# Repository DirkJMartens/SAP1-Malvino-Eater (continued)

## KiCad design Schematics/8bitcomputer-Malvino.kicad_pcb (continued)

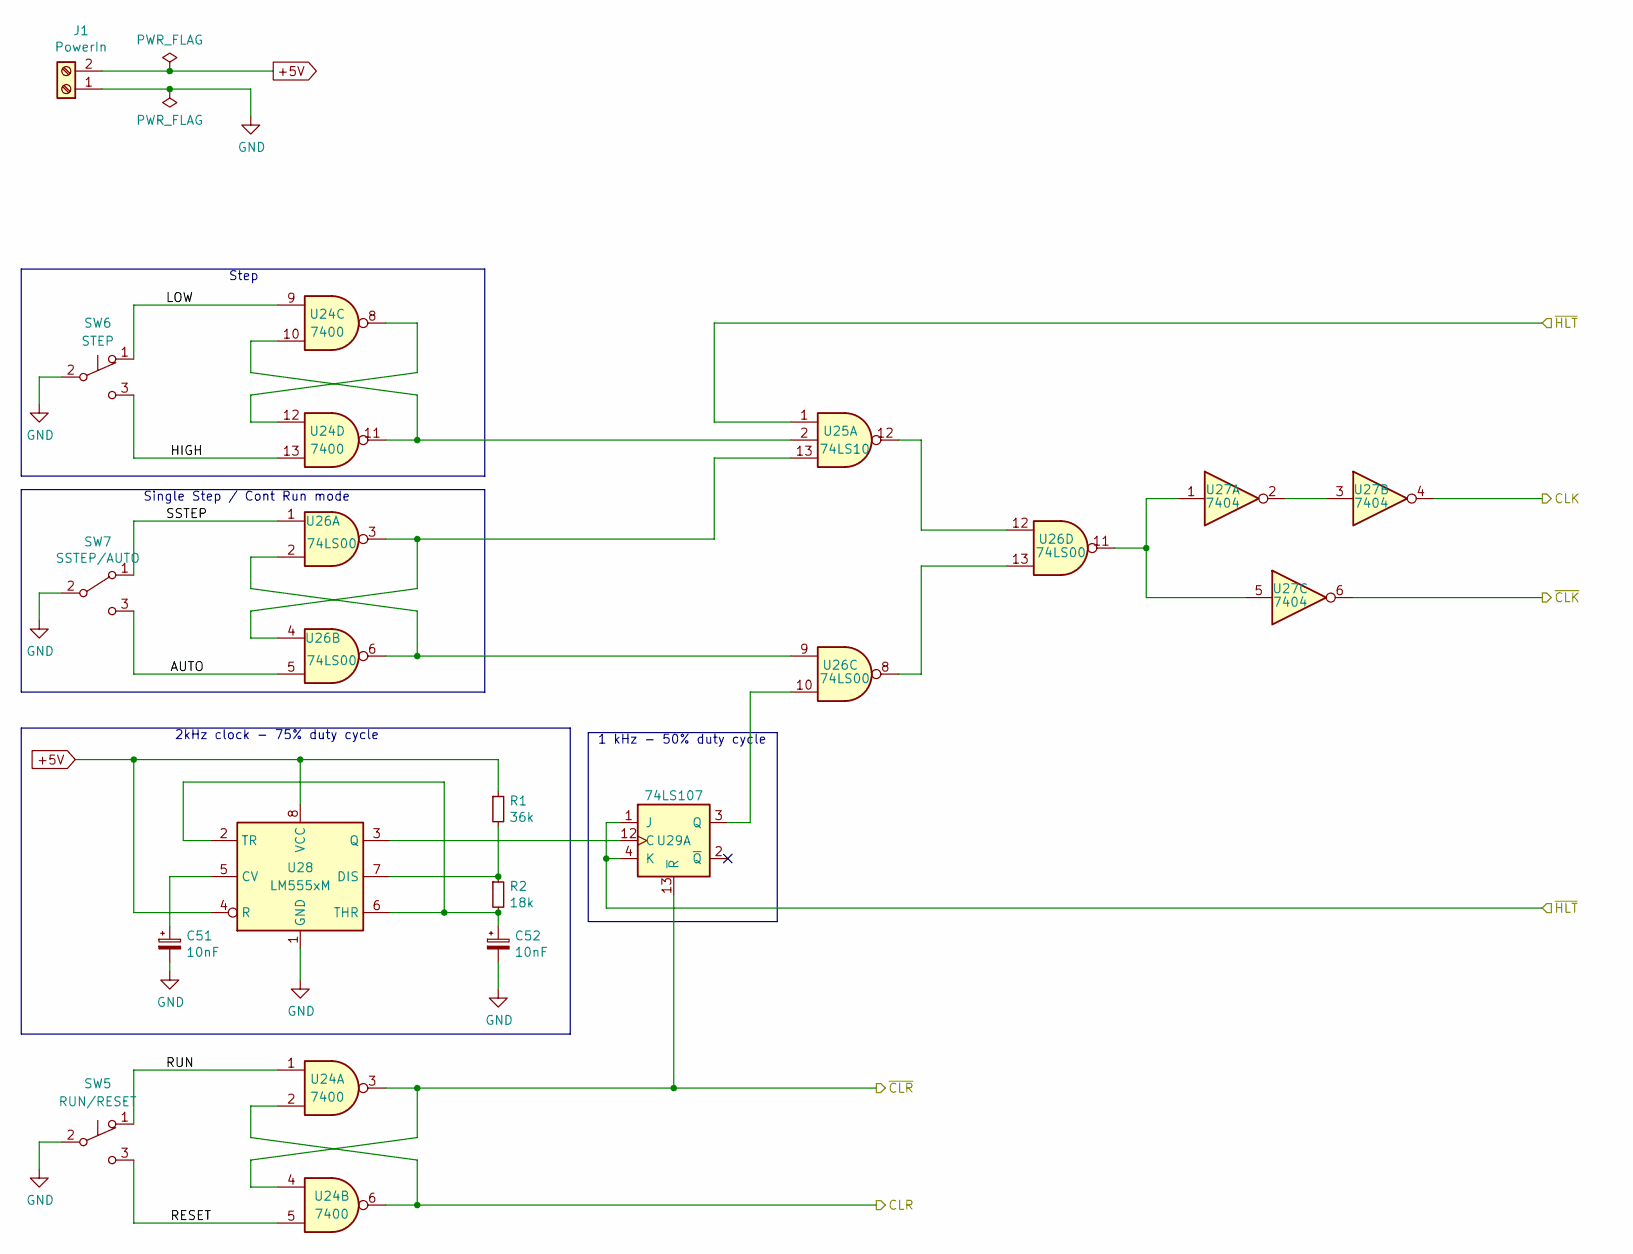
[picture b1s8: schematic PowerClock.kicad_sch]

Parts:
C51, C52: 10nF; C_Disc_D7.5mm_W5.0mm_P7.50mm
J1: PowerIn; TerminalBlock_Phoenix_MKDS-1,5-2-5.08_1x02_P5.08mm_Horizont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
R1: 36k; R_Axial_DIN0207_L6.3mm_D2.5mm_P7.62mm_Horizontal
R2: 18k; R_Axial_DIN0207_L6.3mm_D2.5mm_P7.62mm_Horizontal
SW5: RUN/RESET; SW_Push_1P2T_Vertical_E-Switch_800UDP8P1A1M6
SW6: STEP; SW_CuK_OS102011MA1QN1_SPDT_Angled
SW7: SSTEP/AUTO; TerminalBlock_Phoenix_MKDS-1,5-3-5.08_1x03_P5.08mm_Horizont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
U24: 7400; DIP-14_W7.62mm_LongPads
U25: 74LS10; DIP-14_W7.62mm_LongPads
U26: 74LS00; DIP-14_W7.62mm_LongPads
U27: 7404; DIP-14_W7.62mm_LongPads
U28: LM555xM; DIP-8_W7.62mm_LongPads
U29: 74LS107; DIP-14_W7.62mm_LongPads

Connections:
+5V: J1.2, R1.1, U28.4 (R), U28.8 (VCC); also elsewhere on the board
/1-PowerClock/AUTO: SW7.3 (C), U26.5
/1-PowerClock/CLK: U27.4; also elsewhere on the board
/1-PowerClock/CLR: U24.2, U24.6; also elsewhere on the board
/1-PowerClock/HIGH: SW6.3 (C), U24.13
/1-PowerClock/LOW: SW6.1 (A), U24.9
/1-PowerClock/RESET: SW5.3 (C), U24.5
/1-PowerClock/RUN: SW5.1 (A), U24.1
/1-PowerClock/SSTEP: SW7.1 (A), U26.1
/1-PowerClock/~CLK: U27.6
/1-PowerClock/~CLR: U24.3, U24.4, U29.13 (~R); also elsewhere on the board
/1-PowerClock/~HLT: U25.1, U29.1 (J), U29.4 (K); also elsewhere on the board
GND: C51.2, C52.2, J1.1, SW5.2 (B), SW6.2 (B), SW7.2 (B), U28.1 (GND); also elsewhere on the board
unnamed: C51.1, U28.5 (CV)
unnamed: C52.1, R2.2, U28.2 (TR), U28.6 (THR)
unnamed: R1.2, R2.1, U28.7 (DIS)
unnamed: U24.10, U24.11, U25.2
unnamed: U24.8, U24.12
unnamed: U25.12, U26.12
unnamed: U25.13, U26.3, U26.4
unnamed: U26.2, U26.6, U26.9
unnamed: U26.10, U29.3 (Q)
unnamed: U26.11, U27.1, U27.5
unnamed: U26.8, U26.13
unnamed: U27.2, U27.3
unnamed: U28.3 (Q), U29.12 (C)

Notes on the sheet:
Step
2kHz clock - 75% duty cycle
1 kHz - 50% duty cycle
Single Step / Cont Run mode

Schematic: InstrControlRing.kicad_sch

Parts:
D1, D2, D3, D4, D5, D6: Grn; LED_D3.0mm
D7: Cp; LED_D3.0mm
D8: Ep; LED_D3.0mm
D9: Lm; LED_D3.0mm
D14: CE; LED_D3.0mm
D15: Li; LED_D3.0mm
D16: Ei; LED_D3.0mm
D17: La; LED_D3.0mm
D18: Ea; LED_D3.0mm
D19: Su; LED_D3.0mm
D20: Eu; LED_D3.0mm
D21: Lb; LED_D3.0mm
D22: L0; LED_D3.0mm
D23: HLT; LED_D3.0mm
D24: OUT; LED_D3.0mm
D25: SUB; LED_D3.0mm
D26: ADD; LED_D3.0mm
D27: LDA; LED_D3.0mm
R3, R4, R5, R6, R7, R8, R9, R10, R16, R17, R18, R19, R20, R21, R22, R23, R24, R25, R26, R27, R28, R29, R30: 620; R_0805_2012Metric
U31, U35, U47, U48, U49: 74LS04; DIP-14_W7.62mm_LongPads
U32, U33, U34, U44: 74LS20; DIP-14_W7.62mm_LongPads
U36, U37, U38: 74LS107; DIP-14_W7.62mm_LongPads
U39, U40, U41, U42, U43, U46: 74LS00; DIP-14_W7.62mm_LongPads
U45: 74LS10; DIP-14_W7.62mm_LongPads

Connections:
/1-PowerClock/CLK: U36.9 (C), U36.12 (C), U37.9 (C), U37.12 (C), U38.9 (C), U38.12 (C); also elsewhere on the board
/1-PowerClock/~CLR: U36.10 (~R), U36.13 (~R), U37.10 (~R), U37.13 (~R), U38.10 (~R), U38.13 (~R); also elsewhere on the board
/1-PowerClock/~HLT: D23.2 (A), U34.6; also elsewhere on the board
/2-ProgramCounter/~Ep: U47.2; also elsewhere on the board
/3-InputAndMAR/~Lm: D9.2 (A), U48.6; also elsewhere on the board
/4-16x8RAM/RUN: D14.2 (A), U47.4; also elsewhere on the board
/5-InstructionRegister/I4: U31.9, U32.13, U34.5; also elsewhere on the board
/5-InstructionRegister/I5: U31.5, U33.4, U33.12, U34.4; also elsewhere on the board
/5-InstructionRegister/I6: U31.3, U33.10, U34.2; also elsewhere on the board
/5-InstructionRegister/I7: U31.1, U33.9, U34.1; also elsewhere on the board
/5-InstructionRegister/~Ei: D16.2 (A), U47.8; also elsewhere on the board
/5-InstructionRegister/~Li: D15.2 (A), U47.6; also elsewhere on the board
/6-AccuAddSub/Su: D19.2 (A), U48.2; also elsewhere on the board
/6-AccuAddSub/~Ea: U49.2; also elsewhere on the board
/6-AccuAddSub/~Eu: U49.4; also elsewhere on the board
/6-AccuAddSub/~La: D17.2 (A), U47.10; also elsewhere on the board
/7-RegisterB/~Lb: D21.2 (A), U48.4; also elsewhere on the board
/8-OutputRegister/~Lo: D22.2 (A), U43.8, U48.9; also elsewhere on the board
/9-InstrControlRing/ADD: D26.2 (A), U35.4, U39.4, U40.1, U40.12, U41.9, U42.9, U43.1
/9-InstrControlRing/Ea: D18.2 (A), U47.12, U49.1
/9-InstrControlRing/Eu: D20.2 (A), U46.3, U49.3
/9-InstrControlRing/LDA: D27.2 (A), U35.2, U39.1, U39.12, U40.9, U41.4
/9-InstrControlRing/Lo: U48.8
/9-InstrControlRing/OUT: D24.2 (A), U35.8, U42.1, U43.9
/9-InstrControlRing/SUB: D25.2 (A), U35.6, U39.9, U40.4, U41.1, U41.12, U42.4, U42.12, U43.4
/9-InstrControlRing/T1: D1.2 (A), D8.2 (A), U35.11, U38.1 (J), U38.6 (~Q), U47.1
/9-InstrControlRing/T2: D2.2 (A), D7.2 (A), U37.8 (J), U38.3 (Q); also elsewhere on the board
/9-InstrControlRing/T3: D3.2 (A), U35.13, U37.1 (J), U37.5 (Q), U47.5
/9-InstrControlRing/T4: D4.2 (A), U36.8 (J), U37.3 (Q), U39.2, U39.5, U39.10, U40.10, U40.13, U41.2, U42.2, U43.10
/9-InstrControlRing/T5: D5.2 (A), U36.1 (J), U36.5 (Q), U39.13, U40.2, U40.5, U41.5, U43.2, U43.5
/9-InstrControlRing/T6: D6.2 (A), U36.3 (Q), U38.11 (K), U41.10, U41.13, U42.5, U42.10, U42.13
GND: R3.2, R4.2, R5.2, R6.2, R7.2, R8.2, R9.2, R10.2, R16.2, R17.2, R18.2, R19.2, R20.2, R21.2, R22.2, R23.2, R24.2, R25.2, R26.2, R27.2, R28.2, R29.2, R30.2; also elsewhere on the board
unnamed: D1.1 (K), R3.1
unnamed: D2.1 (K), R4.1
unnamed: D3.1 (K), R5.1
unnamed: D4.1 (K), R6.1
unnamed: D5.1 (K), R7.1
unnamed: D6.1 (K), R8.1
unnamed: D7.1 (K), R9.1
unnamed: D8.1 (K), R10.1
unnamed: D9.1 (K), R16.1
unnamed: D14.1 (K), R17.1
unnamed: D15.1 (K), R18.1
unnamed: D16.1 (K), R19.1
unnamed: D17.1 (K), R20.1
unnamed: D18.1 (K), R21.1
unnamed: D19.1 (K), R22.1
unnamed: D20.1 (K), R23.1
unnamed: D21.1 (K), R24.1
unnamed: D22.1 (K), R25.1
unnamed: D23.1 (K), R26.1
unnamed: D24.1 (K), R27.1
unnamed: D25.1 (K), R28.1
unnamed: D26.1 (K), R29.1
unnamed: D27.1 (K), R30.1
unnamed: U31.2, U32.1, U32.9, U33.1
unnamed: U31.4, U32.2, U32.10, U33.2
unnamed: U31.6, U32.4, U32.12
unnamed: U31.8, U32.5, U33.5, U33.13
unnamed: U32.6, U35.1
unnamed: U32.8, U35.3
unnamed: U33.6, U35.5
unnamed: U33.8, U35.9
unnamed: U35.10, U44.1
unnamed: U35.12, U44.9
unnamed: U36.2 (~Q), U38.8 (J)
unnamed: U36.4 (K), U36.6 (~Q)
unnamed: U36.11 (K), U37.2 (~Q)
unnamed: U37.4 (K), U37.6 (~Q)
unnamed: U37.11 (K), U38.2 (~Q)
unnamed: U38.4 (K), U38.5 (Q)
unnamed: U39.3, U44.2
unnamed: U39.6, U44.4
unnamed: U39.8, U44.5
unnamed: U39.11, U44.10
unnamed: U40.3, U44.12
unnamed: U40.6, U44.13
unnamed: U40.8, U45.13
unnamed: U40.11, U45.2
unnamed: U41.3, U45.1
unnamed: U41.6, U45.5
unnamed: U41.8, U45.4
unnamed: U41.11, U45.3
unnamed: U42.3, U47.13
unnamed: U42.6, U48.1
unnamed: U42.8, U46.1
unnamed: U42.11, U46.2
unnamed: U43.3, U46.4
unnamed: U43.6, U46.5
unnamed: U44.6, U48.5
unnamed: U44.8, U47.3
unnamed: U45.6, U47.11
unnamed: U45.12, U47.9
unnamed: U46.6, U48.3

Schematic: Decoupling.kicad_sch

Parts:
C1, C2, C3, C4, C5, C6, C7, C8, C9, C10, C11, C12, C13, C14, C15, C16, C17, C18, C19, C20, C21, C22, C23, C24, C25, C26, C27, C28, C29, C31, C32, C33, C34, C35, C36, C37, C38, C39, C40, C41, C42, C43, C44, C45, C46, C47, C48: 100nF; C_0805_2012Metric
U1, U2, U29: 74LS107; DIP-14_W7.62mm_LongPads
U24: 7400; DIP-14_W7.62mm_LongPads
U25, U45: 74LS10; DIP-14_W7.62mm_LongPads
U26: 74LS00; DIP-14_W7.62mm_LongPads
U27: 7404; DIP-14_W7.62mm_LongPads
U32, U33, U34, U44: 74LS20; DIP-14_W7.62mm_LongPads

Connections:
+5: C6.1, C7.1; also elsewhere on the board
+5V: C1.1, C2.1, C3.1, C4.1, C5.1, C8.1, C9.1, C10.1, C11.1, C12.1, C13.1, C14.1, C15.1, C16.1, C17.1, C18.1, C19.1, C20.1, C21.1, C22.1, C23.1, C24.1, C25.1, C26.1, C27.1, C28.1, C29.1, C31.1, C32.1, C33.1, C34.1, C35.1, C36.1, C37.1, C38.1, C39.1, C40.1, C41.1, C42.1, C43.1, C44.1, C45.1, C46.1, C47.1, C48.1, U1.14 (VCC), U2.14 (VCC), U24.14 (VCC), U25.14 (VCC), U26.14 (VCC), U27.14 (VCC), U29.14 (VCC), U32.14 (VCC), U33.14 (VCC), U34.14 (VCC), U44.14 (VCC), U45.14 (VCC); also elsewhere on the board
GND: C1.2, C2.2, C3.2, C4.2, C5.2, C6.2, C7.2, C8.2, C9.2, C10.2, C11.2, C12.2, C13.2, C14.2, C15.2, C16.2, C17.2, C18.2, C19.2, C20.2, C21.2, C22.2, C23.2, C24.2, C25.2, C26.2, C27.2, C28.2, C29.2, C31.2, C32.2, C33.2, C34.2, C35.2, C36.2, C37.2, C38.2, C39.2, C40.2, C41.2, C42.2, C43.2, C44.2, C45.2, C46.2, C47.2, C48.2, U1.7 (GND), U2.7 (GND), U24.7 (GND), U25.7 (GND), U26.7 (GND), U27.7 (GND), U29.7 (GND), U32.7 (GND), U33.7 (GND), U34.7 (GND), U44.7 (GND), U45.7 (GND); also elsewhere on the board

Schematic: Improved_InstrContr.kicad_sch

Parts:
U101, U102, U103, U104, U105: (no value)

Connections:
unnamed: U101.3, U105.3
unnamed: U101.4, U101.9, U103.3, U103.4
unnamed: U101.5, U102.4
unnamed: U101.6, U103.12, U105.13
unnamed: U101.7 (GND), U102.7 (GND), U103.7 (GND), U104.7 (GND), U105.7 (GND)
unnamed: U101.8, U104.8
unnamed: U101.10, U102.2
unnamed: U101.11, U104.2, U105.9
unnamed: U101.2, U101.12
unnamed: U101.13, U103.6
unnamed: U101.14 (VCC), U102.14 (VCC), U103.14 (VCC), U104.14 (VCC), U105.14 (VCC)
unnamed: U102.1, U103.2
unnamed: U102.5, U103.5
unnamed: U102.6, U103.13, U104.9
unnamed: U102.9, U102.10, U102.12, U102.13, U103.9, U103.10
unnamed: U103.11, U104.5
unnamed: U104.1, U104.11
unnamed: U104.4, U105.11
unnamed: U104.6, U105.1
unnamed: U104.10, U105.5

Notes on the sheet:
Ep = T1 Cp = T2 Li = T3 Lo = Ea = (OUT T4) Lb = (ADD + SUB) T5 Eu = (ADD + SUB) T6 Ei = (ADD + SUB + LDA) T4 Su = (SUB T6) CE = Lb + (LDA T5) + T3 La = Eu + (LDA T5) Lm = Ei + T1

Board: 2 copper layers, 176 parts (0 on the bottom side), 251 nets, no tracks yet.

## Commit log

2023-08-19 Create Schematics
2023-08-19 schematics.pdf
2023-08-19 Pics
2023-08-19 Short project description
2023-08-19 General project description
2023-08-19 Project description
2023-08-19 Pics and video with detailed description
2023-08-19 Detailed description
2023-08-19 Overall view of the SAP1
2023-08-19 Executing a simple program
